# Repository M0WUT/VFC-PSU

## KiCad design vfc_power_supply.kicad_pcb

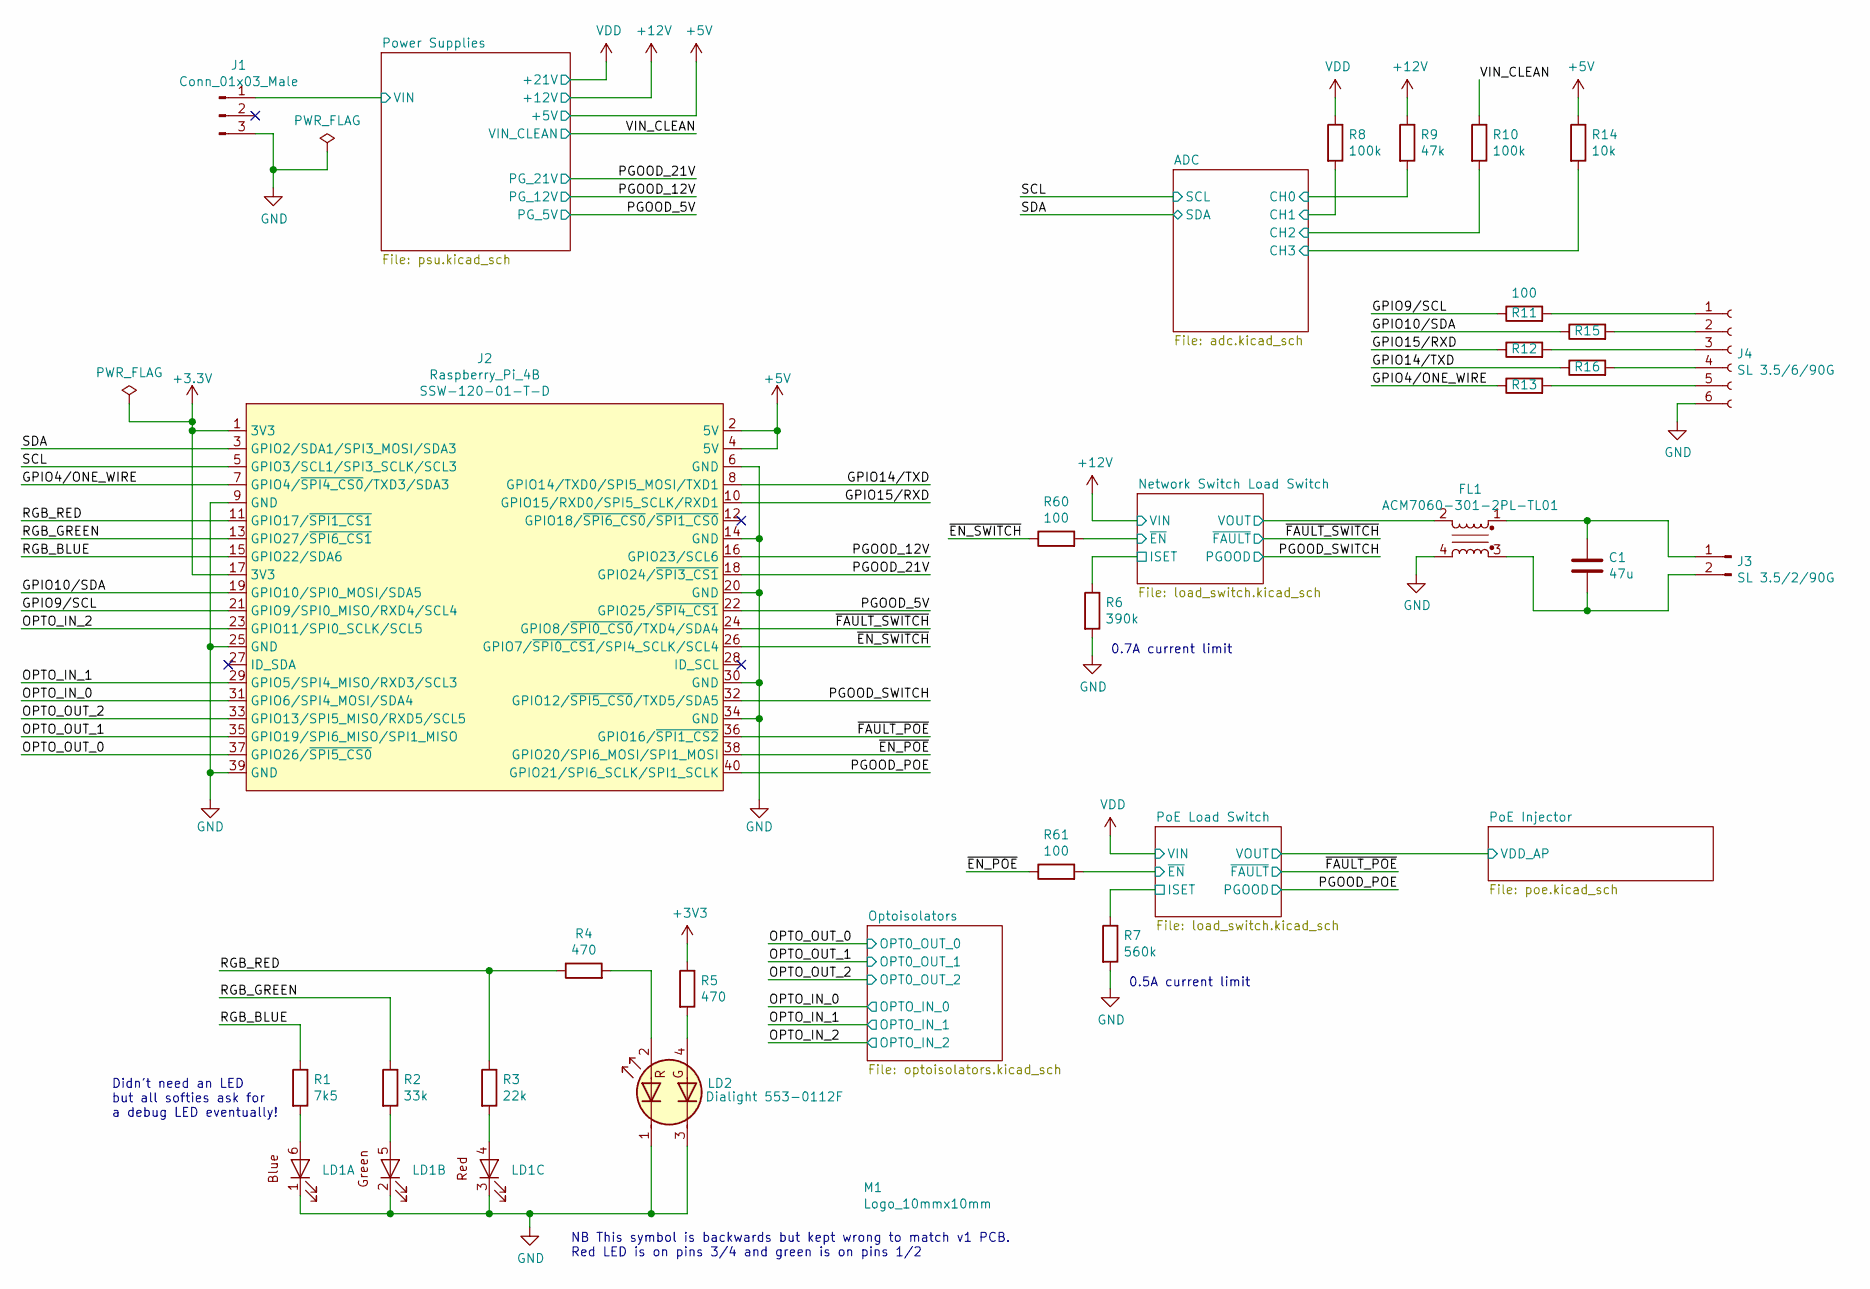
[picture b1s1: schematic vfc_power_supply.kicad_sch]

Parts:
C1: 47u; C_1206_3216Metric
FL1: ACM7060-301-2PL-TL01; TDK_ACM7060-301-2PL-TL01
J1: Conn_01x03_Male; Powerpole_PP30-with-1377G2-PCB-pins-25A_3WAY
J2: Raspberry_Pi_4B; MPN SSW-120-01-T-D
J3: SL 3.5/2/90G; Weidmuller_SL3.5-2-90G
J4: SL 3.5/6/90G; Weidmuller_SL3.5-6-90G
LD1: LED_Cree_CLX6E-FKC
LD2: Dialight 553-0112F; LED_Dialight_553-0112F
M1: Logo_10mmx10mm; Logo_10mmx10mm_Monocle
R1: 7k5; R_0603_1608Metric
R2: 33k; R_0603_1608Metric
R3: 22k; R_0603_1608Metric
R4, R5: 470; R_0603_1608Metric
R6: 390k; R_0603_1608Metric
R7: 560k; R_0603_1608Metric
R8, R10: 100k; R_0603_1608Metric
R9: 47k; R_0603_1608Metric
R11, R12, R13, R15, R16: 100; R_0603_1608Metric
R14: 10k; R_0603_1608Metric
R60, R61: 100; R_0402_1005Metric

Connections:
+5V: J2.2 (5V), J2.4 (5V), R14.1; also elsewhere on the board
+12V: R9.1; also elsewhere on the board
/ADC/CH0: R9.2; also elsewhere on the board
/ADC/CH1: R8.2; also elsewhere on the board
/ADC/CH2: R10.2; also elsewhere on the board
/ADC/CH3: R14.2; also elsewhere on the board
/GPIO4/ONE_WIRE: J2.7 (GPIO4/~SPI4_CS0~/TXD3/SDA3), R13.1
/GPIO9/SCL: J2.21 (GPIO9/SPI0_MISO/RXD4/SCL4), R11.1
/GPIO10/SDA: J2.19 (GPIO10/SPI0_MOSI/SDA5), R15.1
/GPIO14/TXD: J2.8 (GPIO14/TXD0/SPI5_MOSI/TXD1), R16.1
/GPIO15/RXD: J2.10 (GPIO15/RXD0/SPI5_SCLK/RXD1), R12.1
/Network Switch Load Switch/ISET: R6.1; also elsewhere on the board
/Network Switch Load Switch/VOUT: FL1.2; also elsewhere on the board
/Network Switch Load Switch/~EN: R60.2; also elsewhere on the board
/OPTO_IN_0: J2.31 (GPIO6/SPI4_MOSI/SDA4); also elsewhere on the board
/OPTO_IN_1: J2.29 (GPIO5/SPI4_MISO/RXD3/SCL3); also elsewhere on the board
/OPTO_IN_2: J2.23 (GPIO11/SPI0_SCLK/SCL5); also elsewhere on the board
/OPTO_OUT_0: J2.37 (GPIO26/~SPI5_CS0~); also elsewhere on the board
/OPTO_OUT_1: J2.35 (GPIO19/SPI6_MISO/SPI1_MISO); also elsewhere on the board
/OPTO_OUT_2: J2.33 (GPIO13/SPI5_MISO/RXD5/SCL5); also elsewhere on the board
/PGOOD_5V: J2.22 (GPIO25/~SPI4_CS1~); also elsewhere on the board
/PGOOD_12V: J2.16 (GPIO23/SCL6); also elsewhere on the board
/PGOOD_21V: J2.18 (GPIO24/~SPI3_CS1~); also elsewhere on the board
/PGOOD_POE: J2.40 (GPIO21/SPI6_SCLK/SPI1_SCLK); also elsewhere on the board
/PGOOD_SWITCH: J2.32 (GPIO12/~SPI5_CS0~/TXD5/SDA5); also elsewhere on the board
/PoE Load Switch/ISET: R7.1; also elsewhere on the board
/PoE Load Switch/~EN: R61.2; also elsewhere on the board
/Power Supplies/VIN: J1.1; also elsewhere on the board
/RGB_BLUE: J2.15 (GPIO22/SDA6), R1.1
/RGB_GREEN: J2.13 (GPIO27/~SPI6_CS1), R2.1
/RGB_RED: J2.11 (GPIO17/~SPI1_CS1~), R3.1, R4.1
/SCL: J2.5 (GPIO3/SCL1/SPI3_SCLK/SCL3); also elsewhere on the board
/SDA: J2.3 (GPIO2/SDA1/SPI3_MOSI/SDA3); also elsewhere on the board
/VIN_CLEAN: R10.1; also elsewhere on the board
/~EN_POE: J2.38 (GPIO20/SPI6_MOSI/SPI1_MOSI), R61.1
/~EN_SWITCH: J2.26 (GPIO7/~SPI0_CS1~/SPI4_SCLK/SCL4), R60.1
/~FAULT_POE: J2.36 (GPIO16/~SPI1_CS2~); also elsewhere on the board
/~FAULT_SWITCH: J2.24 (GPIO8/~SPI0_CS0~/TXD4/SDA4); also elsewhere on the board
GND: FL1.4, J1.3, J2.6 (GND), J2.9 (GND), J2.14 (GND), J2.20 (GND), J2.25 (GND), J2.30 (GND), J2.34 (GND), J2.39 (GND), J4.6, LD1.1, LD1.2, LD1.3, LD2.1, LD2.3, R6.2, R7.2; also elsewhere on the board
unnamed: C1.1, FL1.1, J3.1
unnamed: C1.2, FL1.3, J3.2
unnamed: J4.1, R11.2
unnamed: J4.2, R15.2
unnamed: J4.3, R12.2
unnamed: J4.4, R16.2
unnamed: J4.5, R13.2
unnamed: LD1.4, R3.2
unnamed: LD1.5, R2.2
unnamed: LD1.6, R1.2
unnamed: LD2.2, R4.2
unnamed: LD2.4, R5.2
VDD: R8.1; also elsewhere on the board
no_connect_(J1-Pad2): J1.2
no_connect_(J2-Pad12): J2.12 (GPIO18/~SPI6_CS0~/~SPI1_CS0)
no_connect_(J2-Pad27): J2.27 (ID_SDA)
no_connect_(J2-Pad28): J2.28 (ID_SCL)

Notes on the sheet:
Didn't need an LED but all softies ask for a debug LED eventually!
NB This symbol is backwards but kept wrong to match v1 PCB. Red LED is on pins 3/4 and green is on pins 1/2
0.7A current limit
0.5A current limit

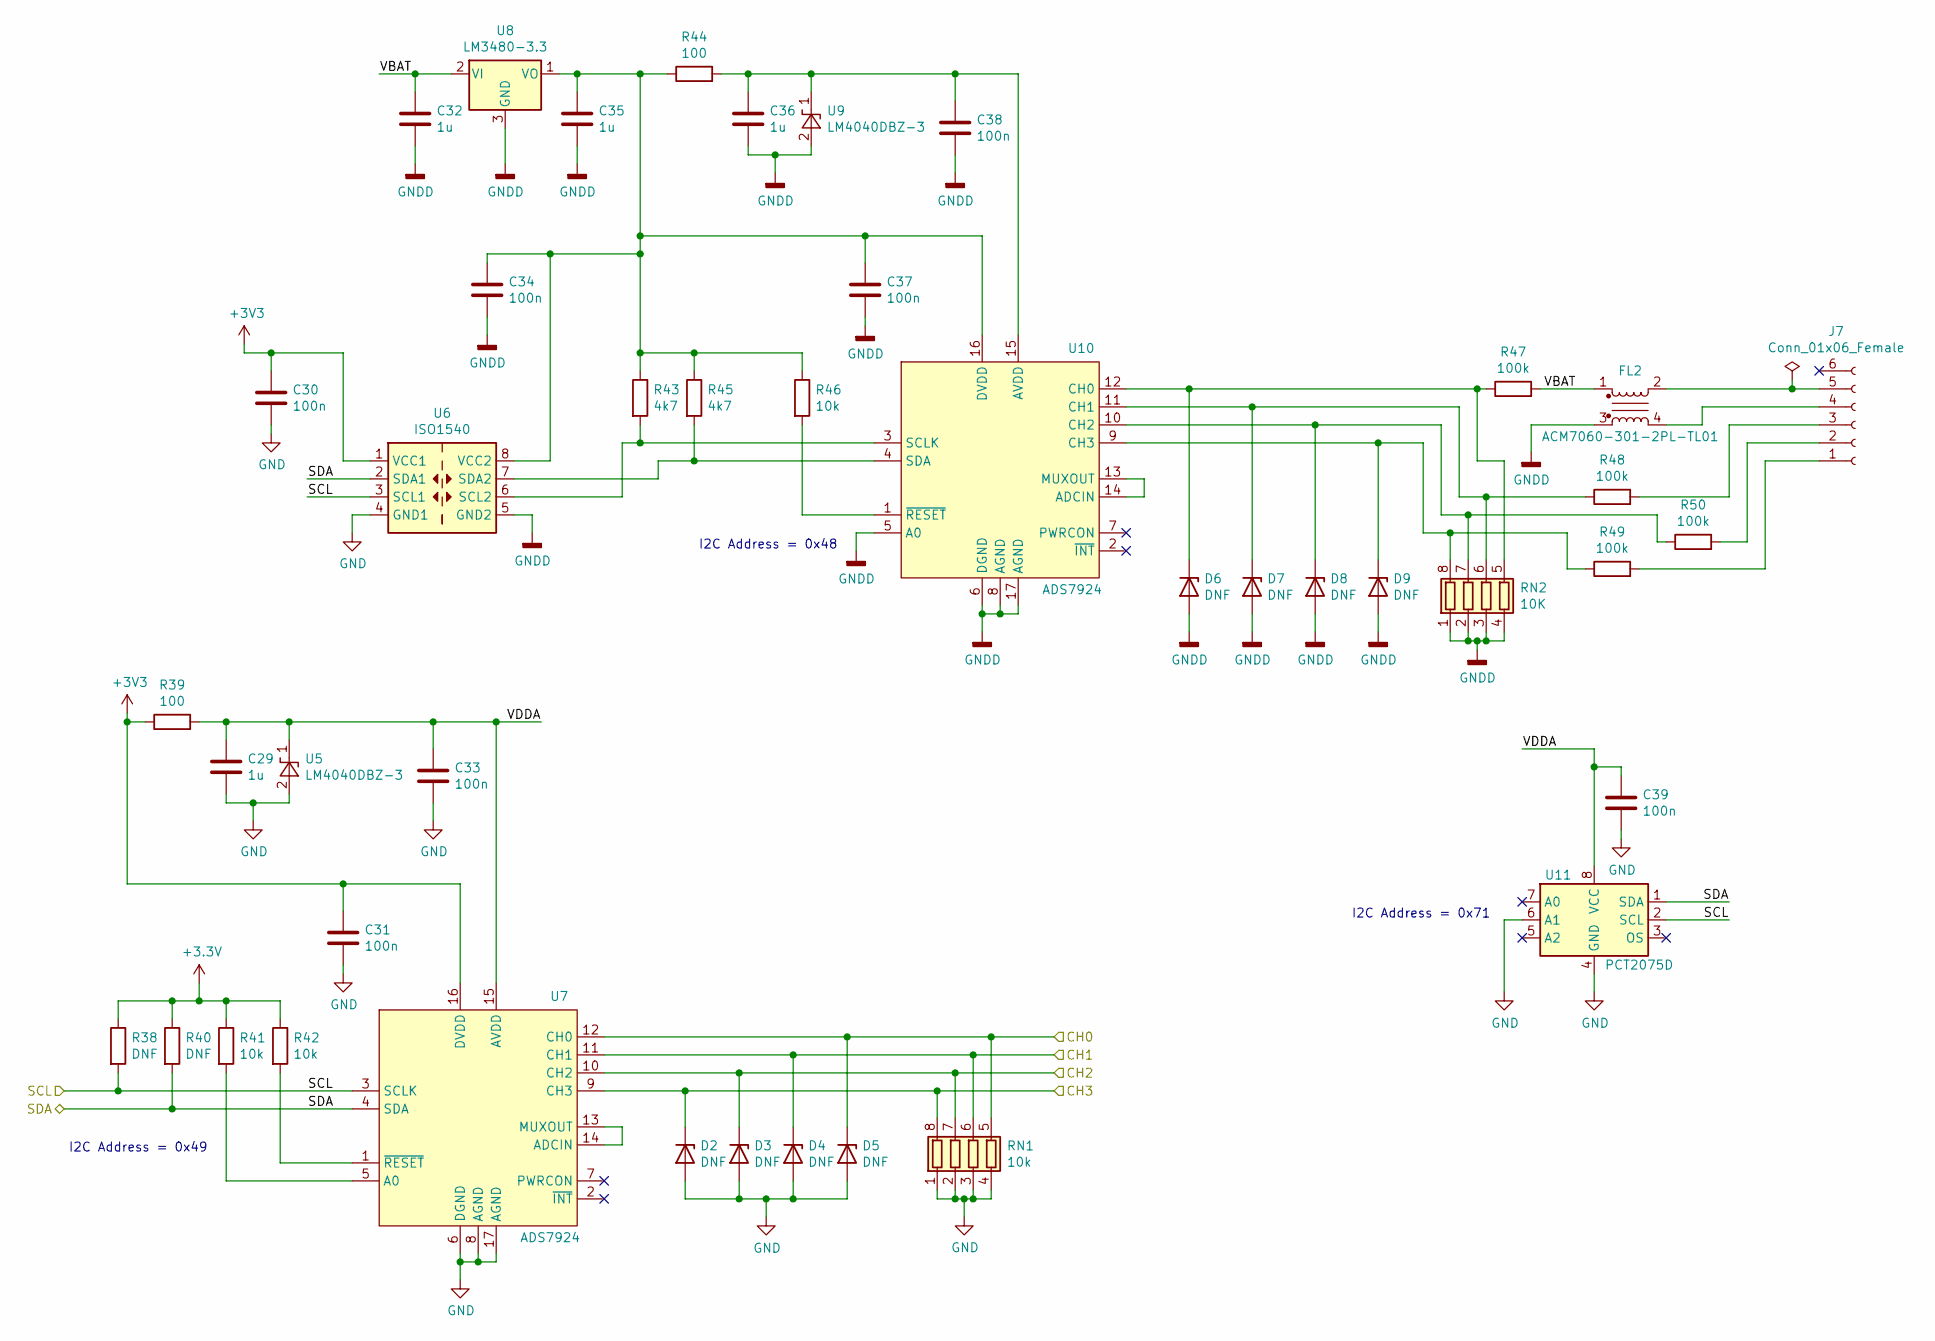
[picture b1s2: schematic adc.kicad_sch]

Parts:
C29, C32, C35, C36: 1u; C_0603_1608Metric
C30, C31, C33, C34, C37, C38, C39: 100n; C_0603_1608Metric
D2, D3, D4, D5, D6, D7, D8, D9: DNF; D_SOD-523
FL2: ACM7060-301-2PL-TL01; TDK_ACM7060-301-2PL-TL01
J7: Conn_01x06_Female; Weidmuller_SL3.5-6-90G
R38, R40: DNF; R_0603_1608Metric
R39, R44: 100; R_0603_1608Metric
R41, R42, R46: 10k; R_0603_1608Metric
R43, R45: 4k7; R_0603_1608Metric
R47, R48, R49, R50: 100k; R_0603_1608Metric
RN1: 10k; R_Cat16-4
RN2: 10K; R_Cat16-4
U5, U9: LM4040DBZ-3; SOT-23
U6: ISO1540; SOIC-8_3.9x4.9mm_P1.27mm
U7, U10: ADS7924; QFN-16-1EP_3x3mm_P0.5mm_EP1.45x1.45mm_ThermalVias
U8: LM3480-3.3; SOT-23
U11: PCT2075D; SOIC-8_3.9x4.9mm_P1.27mm

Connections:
/ADC/CH0: D5.1 (K), RN1.5 (R4.2), U7.12 (CH0); also elsewhere on the board
/ADC/CH1: D4.1 (K), RN1.6 (R3.2), U7.11 (CH1); also elsewhere on the board
/ADC/CH2: D3.1 (K), RN1.7 (R2.2), U7.10 (CH2); also elsewhere on the board
/ADC/CH3: D2.1 (K), RN1.8 (R1.2), U7.9 (CH3); also elsewhere on the board
/ADC/VBAT: C32.1, FL2.1, R47.2, U8.2 (VI)
/ADC/VDDA: C29.1, C33.1, C39.1, R39.2, U5.1 (K), U7.15 (AVDD), U11.8 (VCC)
/SCL: R38.2, U6.3 (SCL1), U7.3 (SCLK), U11.2 (SCL); also elsewhere on the board
/SDA: R40.2, U6.2 (SDA1), U7.4 (SDA), U11.1 (SDA); also elsewhere on the board
GND: C29.2, C30.2, C31.2, C33.2, C39.2, D2.2 (A), D3.2 (A), D4.2 (A), D5.2 (A), RN1.1 (R1.1), RN1.2 (R2.1), RN1.3 (R3.1), RN1.4 (R4.1), U5.2 (A), U6.4 (GND1), U7.6 (DGND), U7.8 (AGND), U7.17 (AGND), U11.4 (GND), U11.6 (A1); also elsewhere on the board
GNDD: C32.2, C34.2, C35.2, C36.2, C37.2, C38.2, D6.2 (A), D7.2 (A), D8.2 (A), D9.2 (A), FL2.3, RN2.1 (R1.1), RN2.2 (R2.1), RN2.3 (R3.1), RN2.4 (R4.1), U6.5 (GND2), U8.3 (GND), U9.2 (A), U10.5 (A0), U10.6 (DGND), U10.8 (AGND), U10.17 (AGND)
unnamed: C34.1, C35.1, C37.1, R43.1, R44.1, R45.1, R46.1, U6.8 (VCC2), U8.1 (VO), U10.16 (DVDD)
unnamed: C36.1, C38.1, R44.2, U9.1 (K), U10.15 (AVDD)
unnamed: D6.1 (K), R47.1, RN2.5 (R4.2), U10.12 (CH0)
unnamed: D7.1 (K), R48.1, RN2.6 (R3.2), U10.11 (CH1)
unnamed: D8.1 (K), R50.1, RN2.7 (R2.2), U10.10 (CH2)
unnamed: D9.1 (K), R49.1, RN2.8 (R1.2), U10.9 (CH3)
unnamed: FL2.2, J7.5
unnamed: FL2.4, J7.4
unnamed: J7.1, R49.2
unnamed: J7.2, R50.2
unnamed: J7.3, R48.2
unnamed: R41.2, U7.5 (A0)
unnamed: R42.2, U7.1 (~RESET)
unnamed: R43.2, U6.6 (SCL2), U10.3 (SCLK)
unnamed: R45.2, U6.7 (SDA2), U10.4 (SDA)
unnamed: R46.2, U10.1 (~RESET)
unnamed: U7.13 (MUXOUT), U7.14 (ADCIN)
unnamed: U10.13 (MUXOUT), U10.14 (ADCIN)
no_connect_(J7-Pad6): J7.6
no_connect_(U7-Pad2): U7.2 (~INT)
no_connect_(U7-Pad7): U7.7 (PWRCON)
no_connect_(U10-Pad2): U10.2 (~INT)
no_connect_(U10-Pad7): U10.7 (PWRCON)
no_connect_(U11-Pad3): U11.3 (OS)
no_connect_(U11-Pad5): U11.5 (A2)
no_connect_(U11-Pad7): U11.7 (A0)

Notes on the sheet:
I2C Address = 0x49
I2C Address = 0x48
I2C Address = 0x71

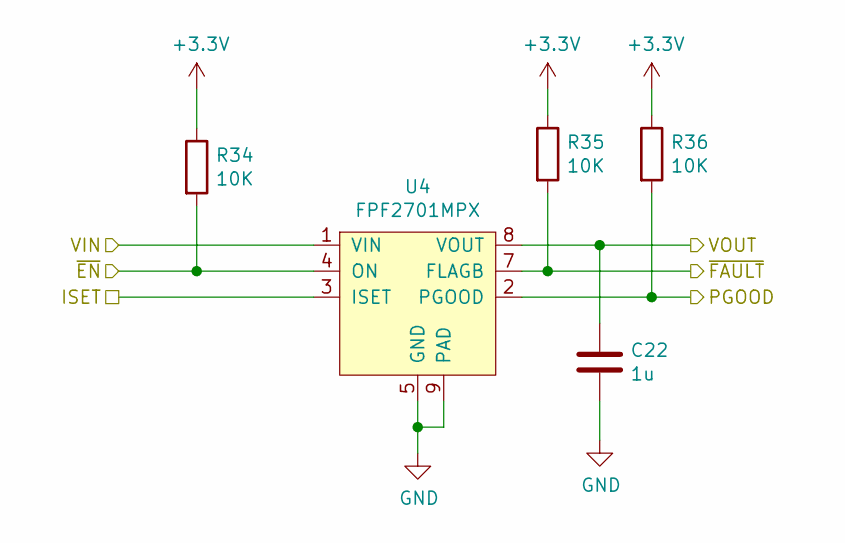
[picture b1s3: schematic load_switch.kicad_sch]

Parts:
C22: 1u; C_0603_1608Metric
R34, R35, R36: 10K; R_0603_1608Metric
U4: FPF2701MPX; WDFN-8-1EP_3x3mm_P0.65mm_EP1.7x2.52mm

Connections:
/PGOOD_POE: R36.2, U4.2 (PGOOD); also elsewhere on the board
/PoE Injector/VDD_AP: C22.1, U4.8 (VOUT); also elsewhere on the board
/PoE Load Switch/ISET: U4.3 (ISET); also elsewhere on the board
/PoE Load Switch/~EN: R34.2, U4.4 (ON); also elsewhere on the board
/~FAULT_POE: R35.2, U4.7 (FLAGB); also elsewhere on the board
GND: C22.2, U4.5 (GND), U4.9 (PAD); also elsewhere on the board
VDD: U4.1 (VIN); also elsewhere on the board

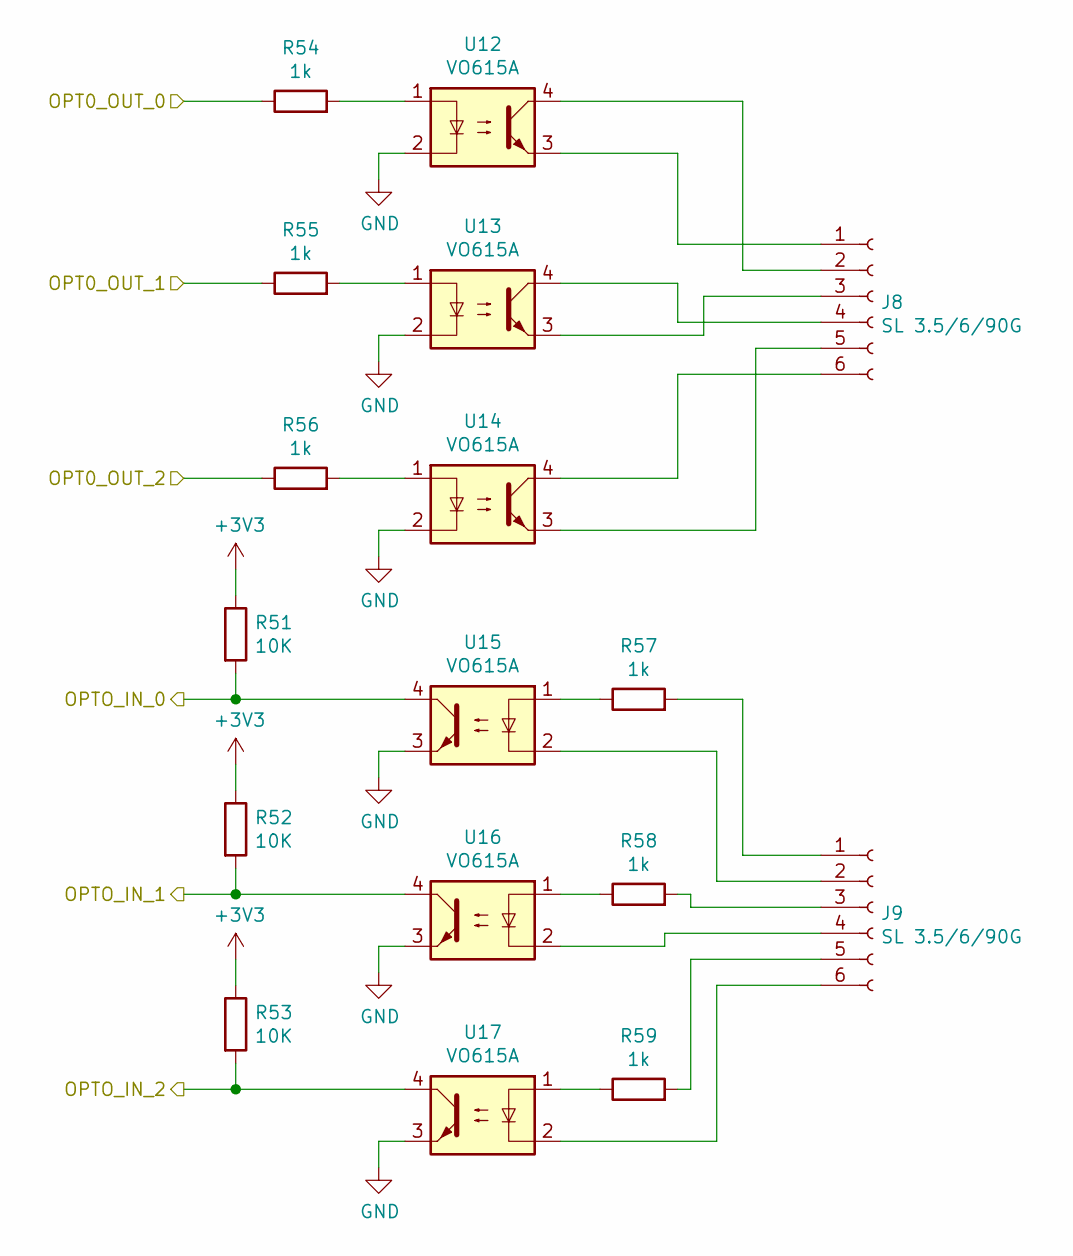
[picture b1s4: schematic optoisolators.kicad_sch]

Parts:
J8, J9: SL 3.5/6/90G; Weidmuller_SL3.5-6-90G
R51, R52, R53: 10K; R_0603_1608Metric
R54, R55, R56, R57, R58, R59: 1k; R_0603_1608Metric
U12, U13, U14, U15, U16, U17: VO615A; DIP-4_W8.89mm_SMDSocket_LongPads

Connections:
/OPTO_IN_0: R51.2, U15.4; also elsewhere on the board
/OPTO_IN_1: R52.2, U16.4; also elsewhere on the board
/OPTO_IN_2: R53.2, U17.4; also elsewhere on the board
/OPTO_OUT_0: R54.1; also elsewhere on the board
/OPTO_OUT_1: R55.1; also elsewhere on the board
/OPTO_OUT_2: R56.1; also elsewhere on the board
GND: U12.2, U13.2, U14.2, U15.3, U16.3, U17.3; also elsewhere on the board
unnamed: J8.1, U12.3
unnamed: J8.2, U12.4
unnamed: J8.3, U13.3
unnamed: J8.4, U13.4
unnamed: J8.5, U14.3
unnamed: J8.6, U14.4
unnamed: J9.1, R57.2
unnamed: J9.2, U15.2
unnamed: J9.3, R58.2
unnamed: J9.4, U16.2
unnamed: J9.5, R59.2
unnamed: J9.6, U17.2
unnamed: R54.2, U12.1
unnamed: R55.2, U13.1
unnamed: R56.2, U14.1
unnamed: R57.1, U15.1
unnamed: R58.1, U16.1
unnamed: R59.1, U17.1

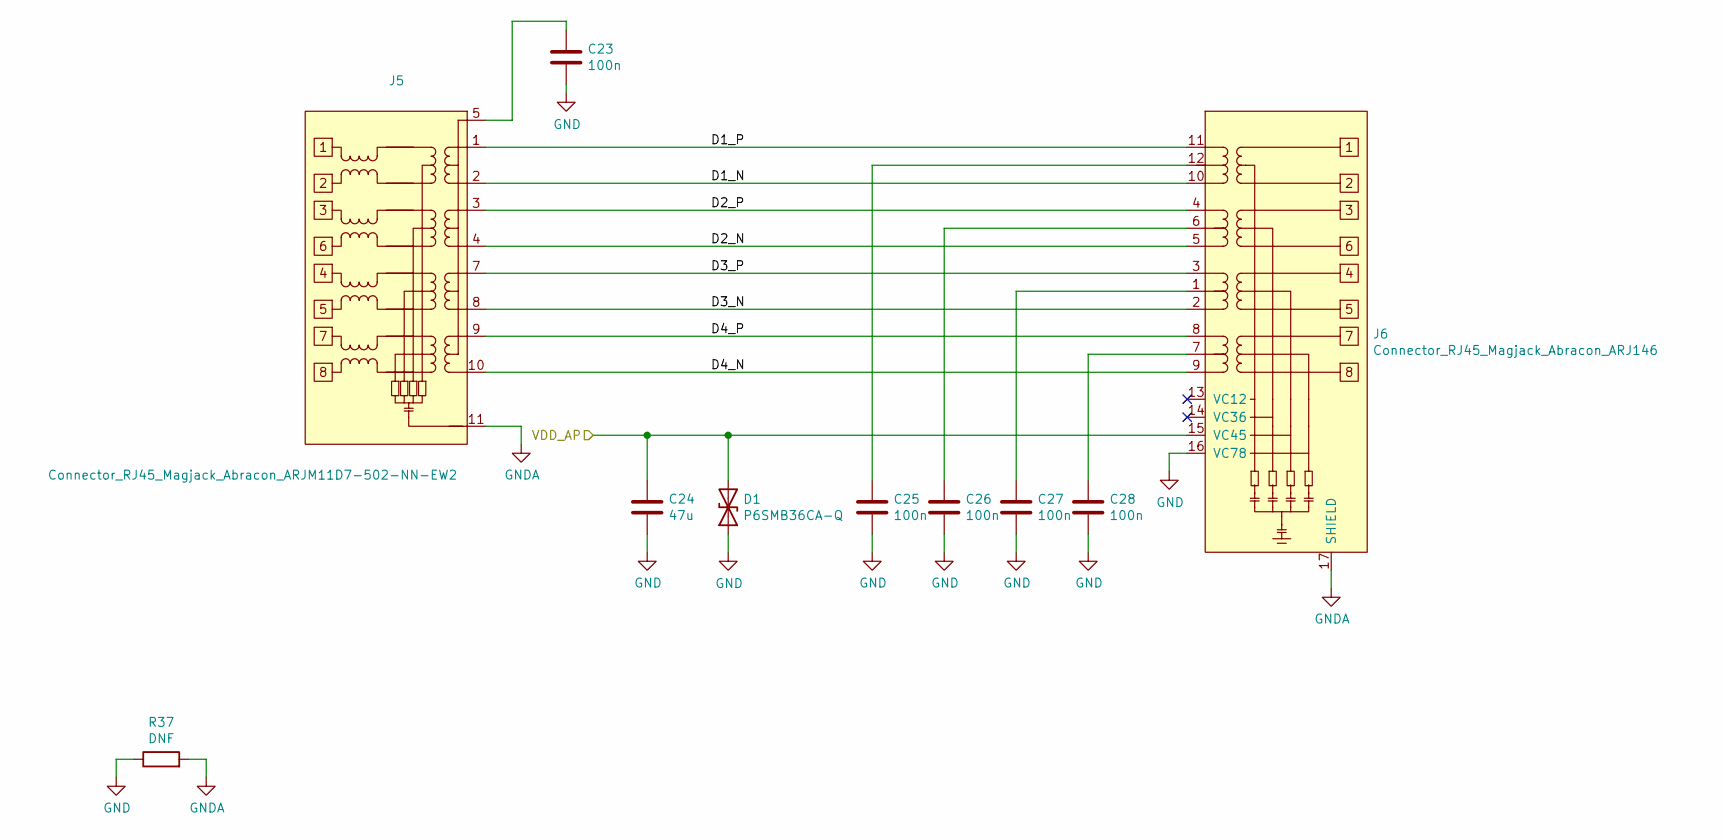
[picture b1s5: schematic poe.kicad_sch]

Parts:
C23, C25, C26, C27, C28: 100n; C_0603_1608Metric
C24: 47u; C_1206_3216Metric
D1: P6SMB36CA-Q; D_SMB
J5: Connector_RJ45_Magjack_Abracon_ARJM11D7-502-NN-EW2
J6: Connector_RJ45_Magjack_Abracon_ARJ146
R37: DNF; R_0603_1608Metric

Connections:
/PoE Injector/D1_N: J5.2, J6.10
/PoE Injector/D1_P: J5.1, J6.11
/PoE Injector/D2_N: J5.4, J6.5
/PoE Injector/D2_P: J5.3, J6.4
/PoE Injector/D3_N: J5.8, J6.2
/PoE Injector/D3_P: J5.7, J6.3
/PoE Injector/D4_N: J5.10, J6.9
/PoE Injector/D4_P: J5.9, J6.8
/PoE Injector/VDD_AP: C24.1, D1.2 (A2), J6.15 (VC45); also elsewhere on the board
GND: C23.2, C24.2, C25.2, C26.2, C27.2, C28.2, D1.1 (A1), J6.16 (VC78), R37.1; also elsewhere on the board
GNDA: J5.11, J6.17 (SHIELD), R37.2
unnamed: C23.1, J5.5, J5.6
unnamed: C25.1, J6.12
unnamed: C26.1, J6.6
unnamed: C27.1, J6.1
unnamed: C28.1, J6.7
no_connect_(J6-Pad13): J6.13 (VC12)
no_connect_(J6-Pad14): J6.14 (VC36)

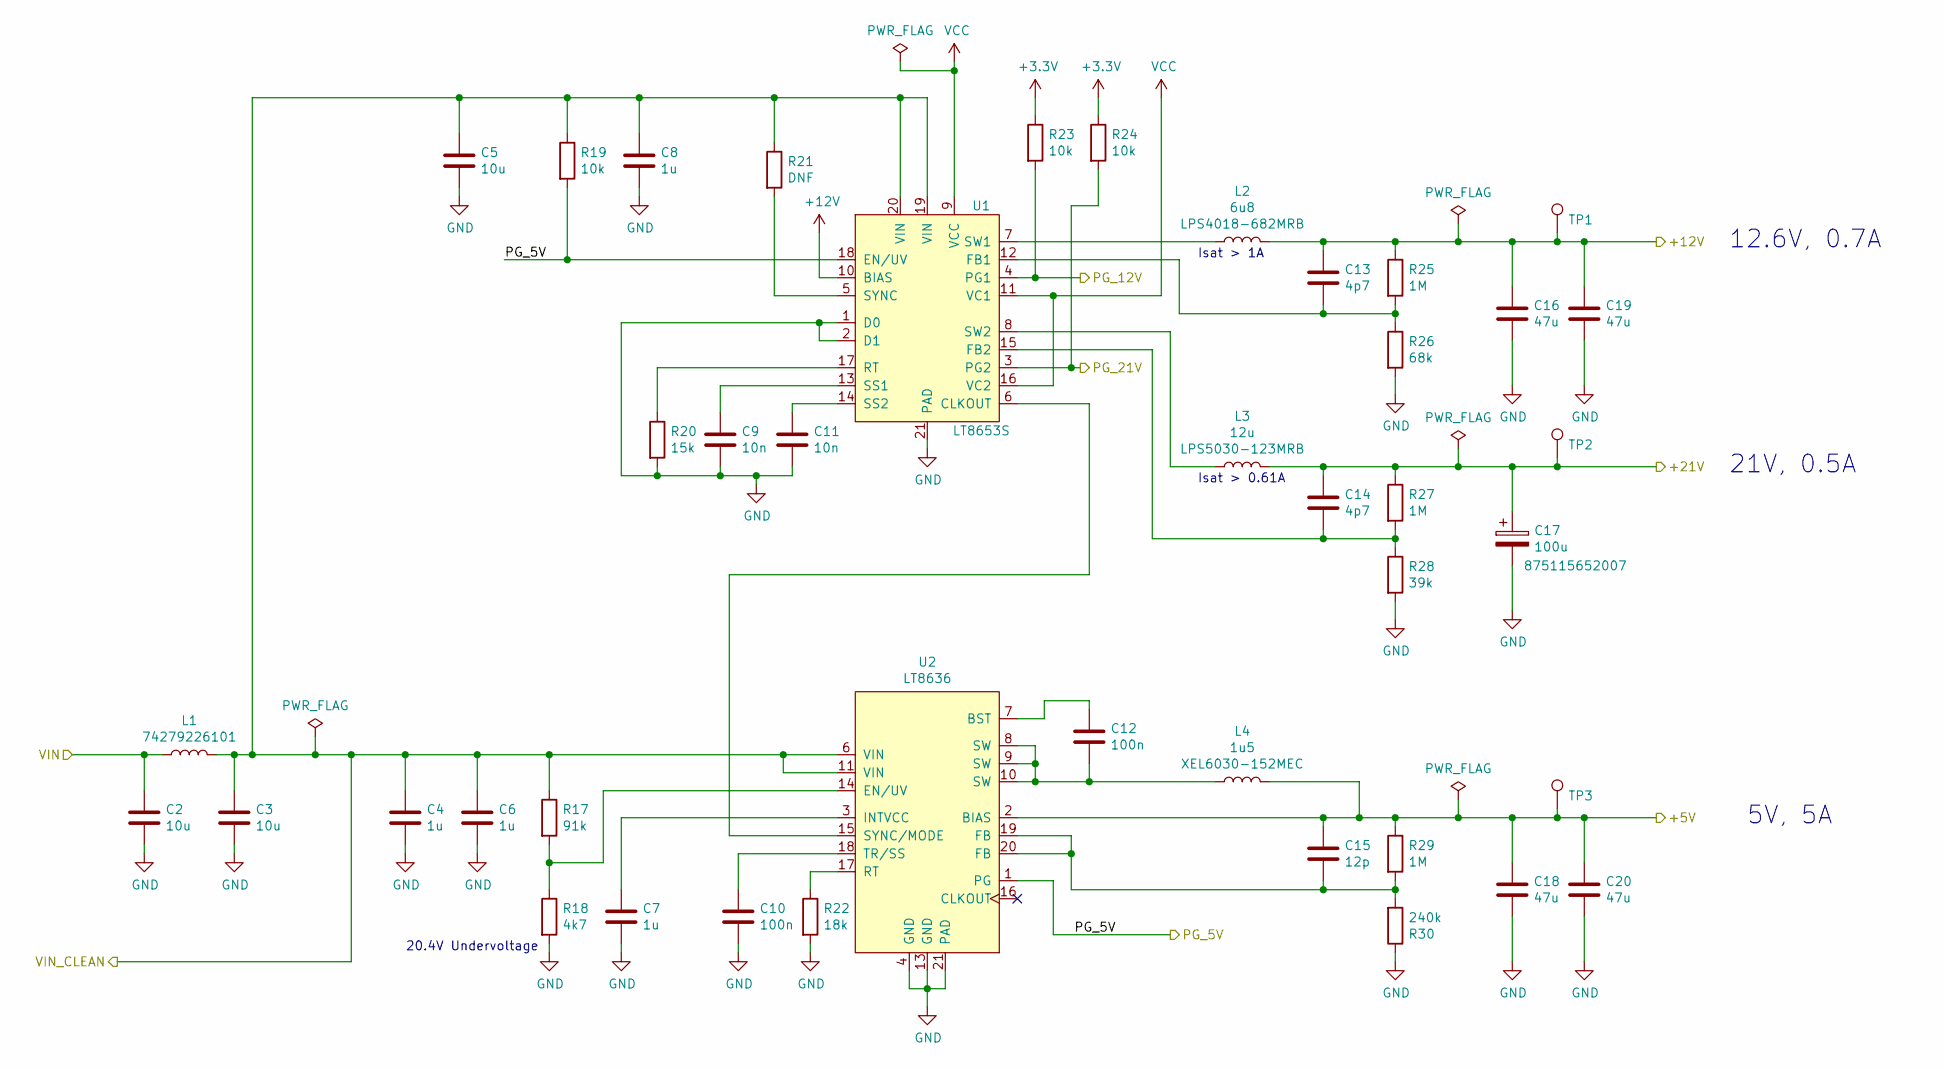
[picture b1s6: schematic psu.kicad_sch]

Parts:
C2, C3, C5: 10u; C_1210_3225Metric
C4, C6, C7, C8: 1u; C_0603_1608Metric
C9, C11: 10n; C_0603_1608Metric
C10, C12: 100n; C_0603_1608Metric
C13, C14: 4p7; C_0603_1608Metric
C15: 12p; C_0603_1608Metric
C16, C18, C19, C20: 47u; C_1206_3216Metric
C17: 100u; Wurth_WCAP_PSHP; MPN 875115652007
L1: 74279226101; L_1812_4532Metric; MPN 74438357047
L2: 6u8; Coilcraft_LPS4018; MPN LPS4018-682MRB
L3: 12u; Coilcraft_LPS5030; MPN LPS5030-123MRB
L4: 1u5; Coilcraft_XEL6030; MPN XEL6030-152MEC
R17: 91k; R_0603_1608Metric
R18: 4k7; R_0603_1608Metric
R19, R23, R24: 10k; R_0603_1608Metric
R20: 15k; R_0603_1608Metric
R21: DNF; R_0603_1608Metric
R22: 18k; R_0603_1608Metric
R25, R27, R29: 1M; R_0603_1608Metric
R26: 68k; R_0603_1608Metric
R28: 39k; R_0603_1608Metric
R30: 240k; R_0603_1608Metric
TP1, TP2, TP3: TestPoint_THTPad_D2.0mm_Drill1.0mm
U1: LT8653S; LQFN-20-1EP_3x4mm_P0.5mm_EP1.4x2.4mm
U2: LT8636; LQFN-20-1EP_3x4mm_P0.5mm_EP1.65x2.65mm

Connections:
+5V: C15.1, C18.1, C20.1, L4.2, R29.1, TP3.1, U2.2 (BIAS); also elsewhere on the board
+12V: C13.1, C16.1, C19.1, L2.2, R25.1, TP1.1, U1.10 (BIAS); also elsewhere on the board
/PGOOD_5V: R19.2, U1.18 (EN/UV), U2.1 (PG); also elsewhere on the board
/PGOOD_12V: R23.2, U1.4 (PG1); also elsewhere on the board
/PGOOD_21V: R24.2, U1.3 (PG2); also elsewhere on the board
/Power Supplies/VIN: C2.1, L1.1; also elsewhere on the board
/VIN_CLEAN: C3.1, C4.1, C5.1, C6.1, C8.1, L1.2, R17.1, R19.1, R21.1, U1.19 (VIN), U1.20 (VIN), U2.6 (VIN), U2.11 (VIN); also elsewhere on the board
GND: C2.2, C3.2, C4.2, C5.2, C6.2, C7.2, C8.2, C9.2, C10.2, C11.2, C16.2, C17.2, C18.2, C19.2, C20.2, R18.2, R20.2, R22.2, R26.2, R28.2, R30.1, U1.1 (D0), U1.2 (D1), U1.21 (PAD), U2.4 (GND), U2.13 (GND), U2.21 (PAD); also elsewhere on the board
unnamed: C7.1, U2.3 (INTVCC)
unnamed: C9.1, U1.13 (SS1)
unnamed: C10.1, U2.18 (TR/SS)
unnamed: C11.1, U1.14 (SS2)
unnamed: C12.1, U2.7 (BST)
unnamed: C12.2, L4.1, U2.8 (SW), U2.9 (SW), U2.10 (SW)
unnamed: C13.2, R25.2, R26.1, U1.12 (FB1)
unnamed: C14.2, R27.2, R28.1, U1.15 (FB2)
unnamed: C15.2, R29.2, R30.2, U2.19 (FB), U2.20 (FB)
unnamed: L2.1, U1.7 (SW1)
unnamed: L3.1, U1.8 (SW2)
unnamed: R17.2, R18.1, U2.14 (EN/UV)
unnamed: R20.1, U1.17 (RT)
unnamed: R21.2, U1.5 (SYNC)
unnamed: R22.1, U2.17 (RT)
unnamed: U1.6 (CLKOUT), U2.15 (SYNC/MODE)
VCC: U1.9 (VCC), U1.11 (VC1), U1.16 (VC2)
VDD: C14.1, C17.1, L3.2, R27.1, TP2.1; also elsewhere on the board
no_connect_(U2-Pad16): U2.16 (CLKOUT)

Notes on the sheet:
20.4V Undervoltage
Isat > 1A
Isat > 0.61A
12.6V, 0.7A
21V, 0.5A
5V, 5A

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
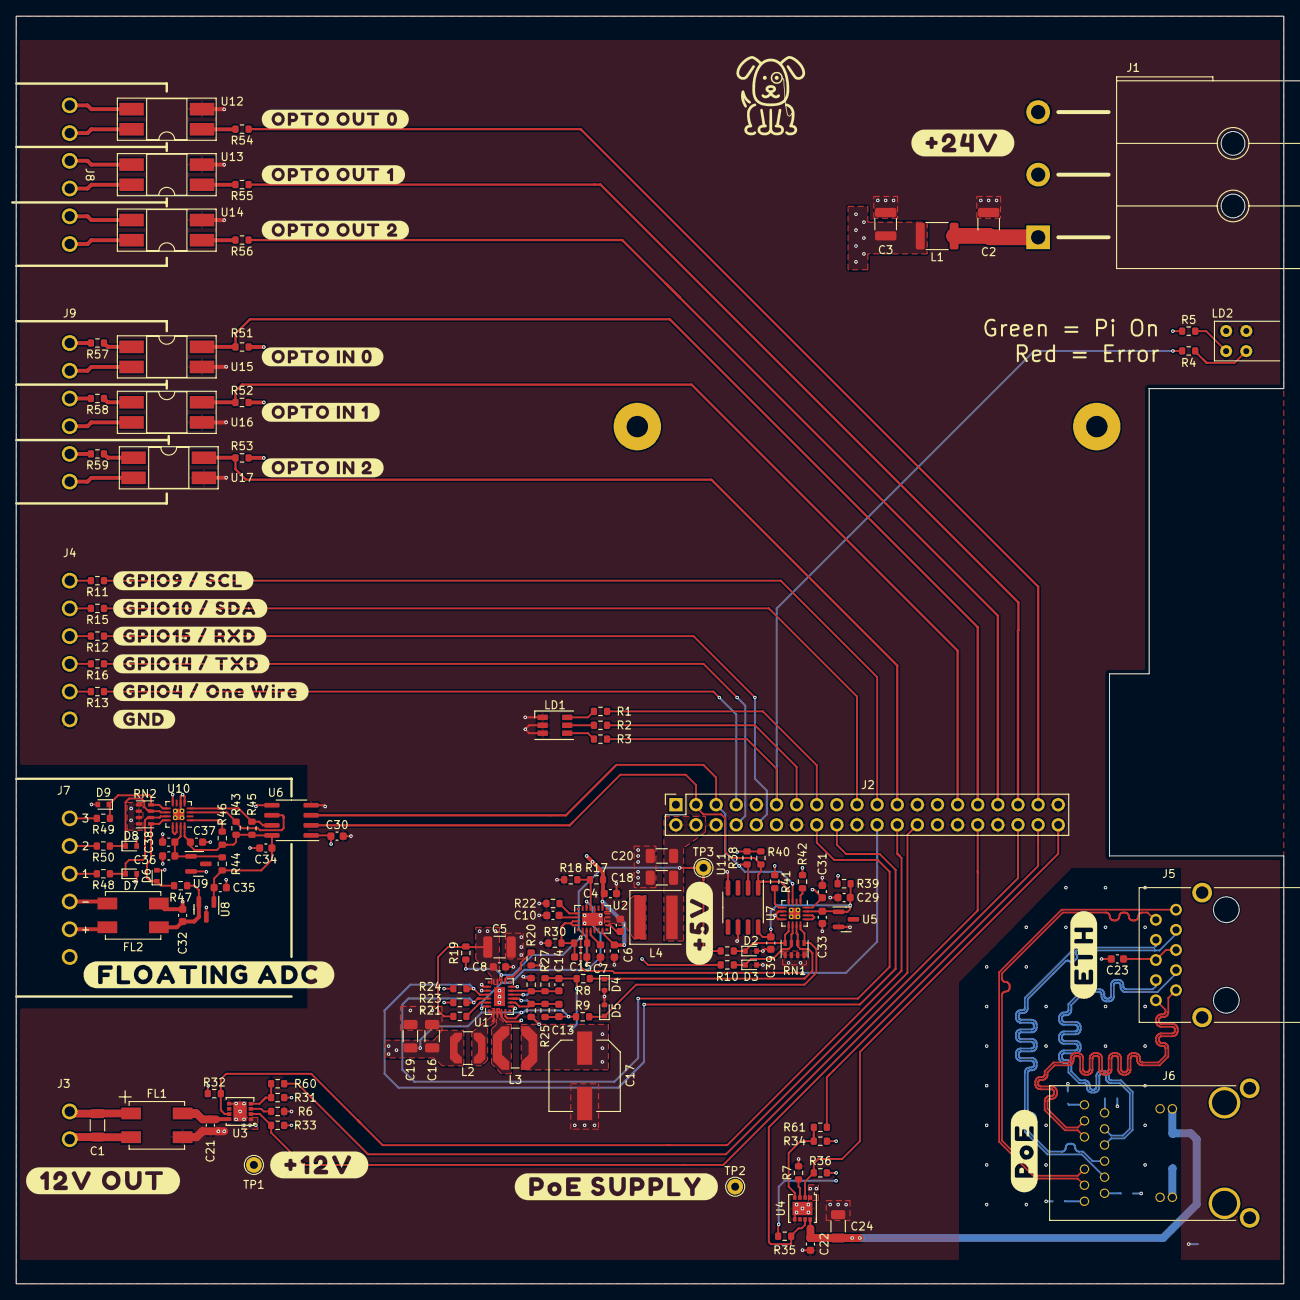
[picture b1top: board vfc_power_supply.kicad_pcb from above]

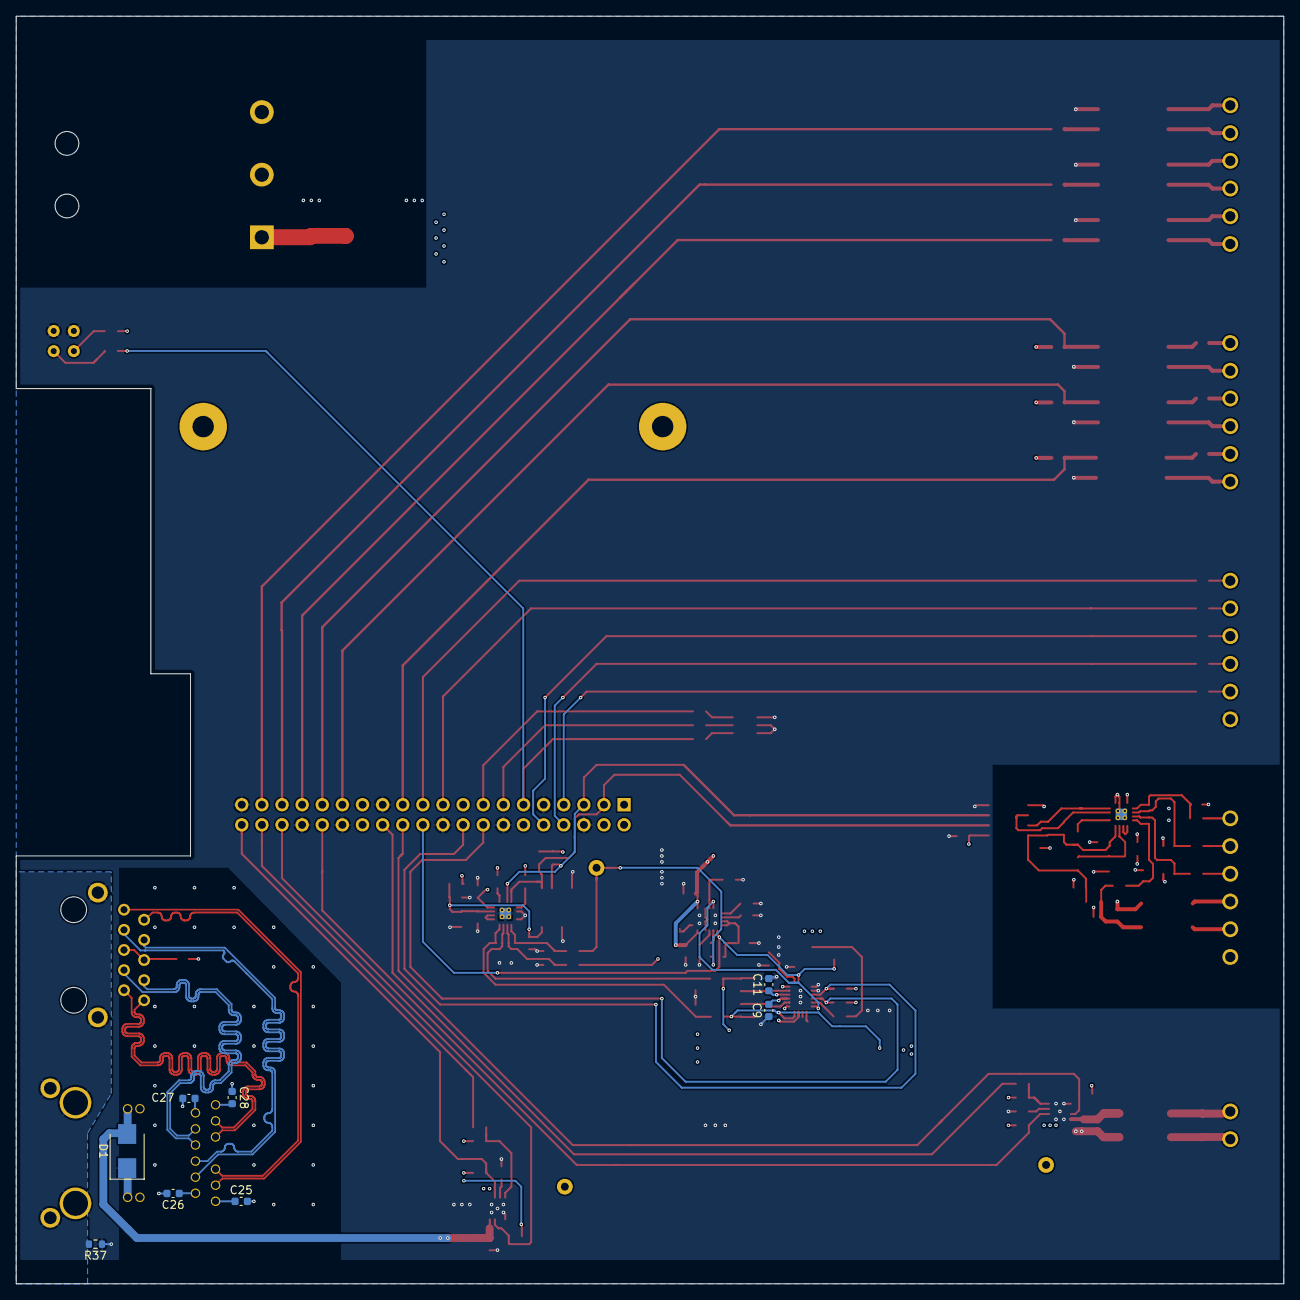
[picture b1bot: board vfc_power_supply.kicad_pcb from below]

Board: 4 copper layers, 160.0 x 160.0 mm, 149 parts (8 on the bottom side), 124 nets.

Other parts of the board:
C21: 1u; C_0603_1608Metric
R31, R32, R33: 10K; R_0603_1608Metric
U3: FPF2701MPX; WDFN-8-1EP_3x3mm_P0.65mm_EP1.7x2.52mm

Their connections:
+12V: U3.1 (VIN); also elsewhere on the board
/Network Switch Load Switch/ISET: U3.3 (ISET); also elsewhere on the board
/Network Switch Load Switch/VOUT: C21.1, U3.8 (VOUT); also elsewhere on the board
/Network Switch Load Switch/~EN: R31.2, U3.4 (ON); also elsewhere on the board
/PGOOD_SWITCH: R33.2, U3.2 (PGOOD); also elsewhere on the board
/~FAULT_SWITCH: R32.2, U3.7 (FLAGB); also elsewhere on the board
GND: C21.2, U3.5 (GND), U3.9 (PAD); also elsewhere on the board

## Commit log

2020-12-05 created
2020-12-06 more progress
2020-12-07 nearly done, just missing output protection
2020-12-08 Added notes to schematic
2020-12-12 Ready for review
2021-01-02 Commit before restarting layout
2021-01-03 Updated library parts
2021-01-06 new layout
2021-01-16 Started new connector layout
2021-01-16 Mostly complete, just missing a few tracks and review
2021-01-21 Finished tidying up silkscreen
2021-01-23 Added changes following review from RMC
2021-03-19 Tweaked component values to working. Added rear panel PCB
2021-03-19 Front and rear layout done
2021-03-20 Added KiBuzzard labels
2023-11-19 Tested actions workflow
2023-11-19 ADded readme
